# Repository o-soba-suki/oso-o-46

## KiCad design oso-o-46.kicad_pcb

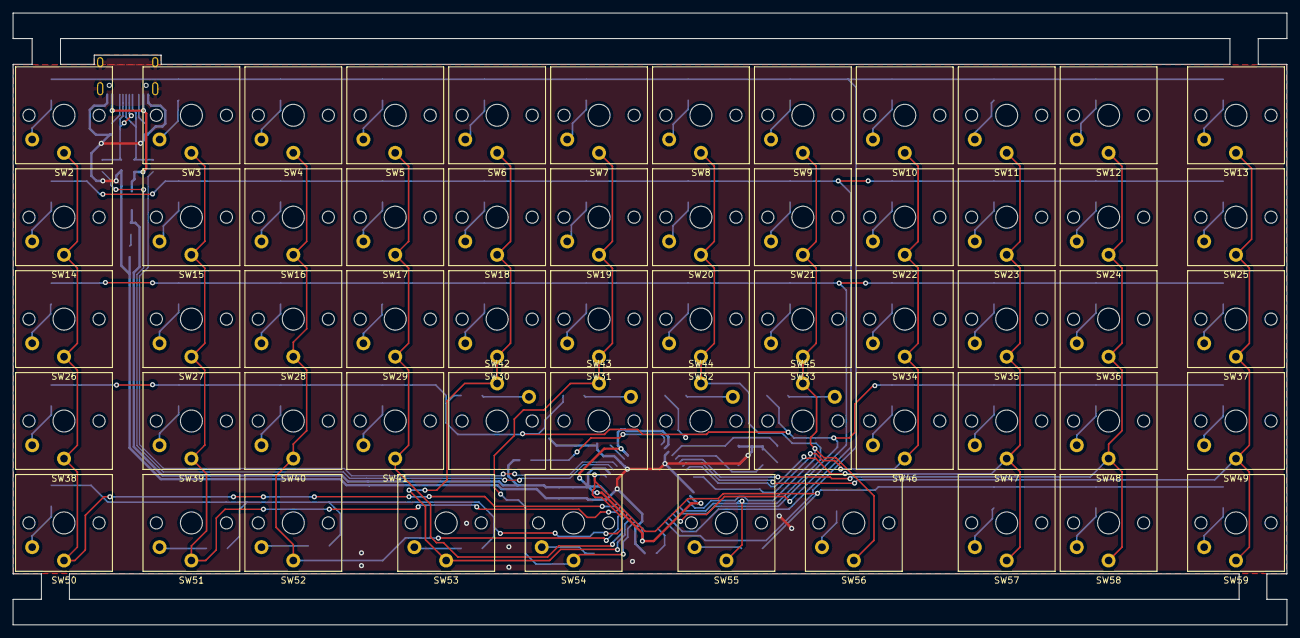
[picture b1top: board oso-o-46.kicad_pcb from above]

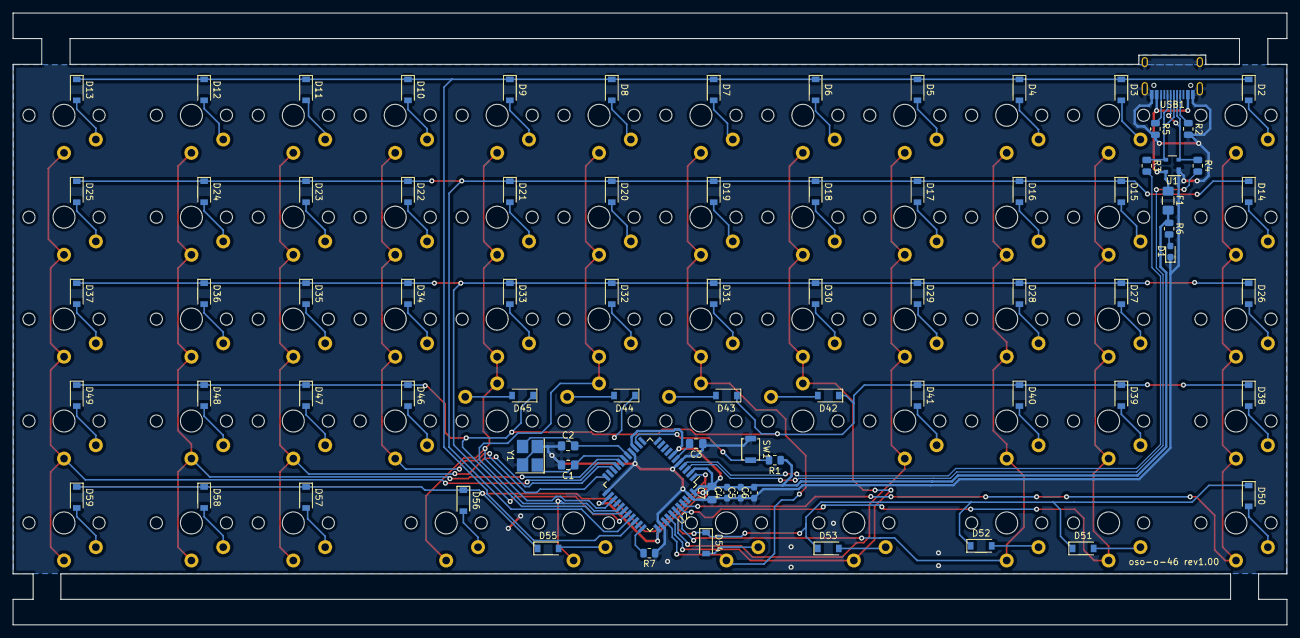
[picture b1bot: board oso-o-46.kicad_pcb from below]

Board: 2 copper layers, 200.0 x 96.0 mm, 137 parts (79 on the bottom side), 90 nets.

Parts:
C1, C2: 22u; C_0805_2012Metric_Pad1.18x1.45mm_HandSolder
C3: 1u; C_0805_2012Metric_Pad1.18x1.45mm_HandSolder
C4, C5, C6: 0.1u; C_0603_1608Metric_Pad1.08x0.95mm_HandSolder
C7: 10u; C_0805_2012Metric_Pad1.18x1.45mm_HandSolder
D1: LED; LED_0603_1608Metric_Pad1.05x0.95mm_HandSolder
D2, D3, D4, D5, D6, D7, D8, D9, D10, D11, D12, D13, D14, D15, D16, D17, D18, D19, D20, D21, D22, D23, D24, D25, D26, D27, D28, D29, D30, D31, D32, D33, D34, D35, D36, D37, D38, D39, D40, D41, D42, D43, D44, D45, D46, D47, D48, D49, D50, D51, D52, D53, D54, D55, D56, D57, D58, D59: D; D_SOD-123
F1: ASMD1206-150; Fuse_1206_3216Metric_Pad1.42x1.75mm_HandSolder
R1, R7: 10k; R_0805_2012Metric
R2, R5: 5.1k; R_0805_2012Metric
R3, R4: 22; R_0805_2012Metric
R6: 1k; R_0805_2012Metric
SW1: SW_Push; SW_SPST_B3U-1000P
SW2, SW3, SW4, SW5, SW6, SW7, SW8, SW9, SW10, SW11, SW12, SW13, SW14, SW15, SW16, SW17, SW18, SW19, SW20, SW21, SW22, SW23, SW24, SW25, SW26, SW27, SW28, SW29, SW30, SW31, SW32, SW33, SW34, SW35, SW36, SW37, SW38, SW39, SW40, SW41, SW42, SW43, SW44, SW45, SW46, SW47, SW48, SW49, SW50, SW51, SW52, SW53, SW54, SW55, SW56, SW57, SW58, SW59: SW_PUSH; SW_Kailh_Choc_V1
U1: PRTR5V0U2X; SOT-143
U2: ATmega32U4-A; TQFP-44_10x10mm_P0.8mm
USB1: HRO-TYPE-C-31-M-12; HRO-TYPE-C-31-M-12-Assembly
Y1: 16HMz; Crystal_SMD_3225-4Pin_3.2x2.5mm_HandSoldering

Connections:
+5V: C4.2, C5.2, C6.2, C7.2, F1.2, R1.1, R6.1, U2.2 (UVCC), U2.7 (VBUS), U2.14 (VCC), U2.24 (AVCC), U2.34 (VCC), U2.44 (AVCC)
COL01: SW2.1, SW14.1, SW26.1, SW38.1, SW50.1, U2.41 (PF0)
COL02: SW3.1, SW15.1, SW27.1, SW39.1, SW51.1, U2.40 (PF1)
COL03: SW4.1, SW16.1, SW28.1, SW40.1, SW52.1, U2.39 (PF4)
COL04: SW5.1, SW17.1, SW29.1, SW41.1, U2.38 (PF5)
COL05: SW6.1, SW18.1, SW30.1, SW42.1, SW53.1, U2.37 (PF6)
COL06: SW7.1, SW19.1, SW31.1, SW43.1, SW54.1, U2.36 (PF7)
COL07: SW8.1, SW20.1, SW32.1, SW44.1, SW55.1, U2.27 (PD7)
COL08: SW9.1, SW21.1, SW33.1, SW45.1, SW56.1, U2.25 (PD4)
COL09: SW10.1, SW22.1, SW34.1, SW46.1, U2.22 (PD5)
COL10: SW11.1, SW23.1, SW35.1, SW47.1, SW57.1, U2.20 (PD2)
COL11: SW12.1, SW24.1, SW36.1, SW48.1, SW58.1, U2.18 (PD0)
COL12: SW13.1, SW25.1, SW37.1, SW49.1, SW59.1, U2.19 (PD1)
D+: R3.2, U2.4 (D+)
D-: R4.2, U2.3 (D-)
GND: C1.2, C2.1, C3.1, C4.1, C5.1, C6.1, C7.1, D1.1 (K), R2.2, R5.2, R7.1, SW1.1, U1.1 (GND), U2.5 (UGND), U2.15 (GND), U2.23 (GND), U2.35 (GND), U2.43 (GND), USB1.1 (GND), USB1.12 (GND), USB1.13 (SHIELD), Y1.2, Y1.4
unnamed: C1.1, U2.17 (XTAL1), Y1.1
unnamed: C2.2, U2.16 (XTAL2), Y1.3
unnamed: C3.2, U2.6 (UCAP)
unnamed: D1.2 (A), R6.2
unnamed: D2.2 (A), SW2.2
unnamed: D3.2 (A), SW3.2
unnamed: D4.2 (A), SW4.2
unnamed: D5.2 (A), SW5.2
unnamed: D6.2 (A), SW6.2
unnamed: D7.2 (A), SW7.2
unnamed: D8.2 (A), SW8.2
unnamed: D9.2 (A), SW9.2
unnamed: D10.2 (A), SW10.2
unnamed: D11.2 (A), SW11.2
unnamed: D12.2 (A), SW12.2
unnamed: D13.2 (A), SW13.2
unnamed: D14.2 (A), SW14.2
unnamed: D15.2 (A), SW15.2
unnamed: D16.2 (A), SW16.2
unnamed: D17.2 (A), SW17.2
unnamed: D18.2 (A), SW18.2
unnamed: D19.2 (A), SW19.2
unnamed: D20.2 (A), SW20.2
unnamed: D21.2 (A), SW21.2
unnamed: D22.2 (A), SW22.2
unnamed: D23.2 (A), SW23.2
unnamed: D24.2 (A), SW24.2
unnamed: D25.2 (A), SW25.2
unnamed: D26.2 (A), SW26.2
unnamed: D27.2 (A), SW27.2
unnamed: D28.2 (A), SW28.2
unnamed: D29.2 (A), SW29.2
unnamed: D30.2 (A), SW30.2
unnamed: D31.2 (A), SW31.2
unnamed: D32.2 (A), SW32.2
unnamed: D33.2 (A), SW33.2
unnamed: D34.2 (A), SW34.2
unnamed: D35.2 (A), SW35.2
unnamed: D36.2 (A), SW36.2
unnamed: D37.2 (A), SW37.2
unnamed: D38.2 (A), SW38.2
unnamed: D39.2 (A), SW39.2
unnamed: D40.2 (A), SW40.2
unnamed: D41.2 (A), SW41.2
unnamed: D42.2 (A), SW42.2
unnamed: D43.2 (A), SW43.2
unnamed: D44.2 (A), SW44.2
unnamed: D45.2 (A), SW45.2
unnamed: D46.2 (A), SW46.2
unnamed: D47.2 (A), SW47.2
unnamed: D48.2 (A), SW48.2
unnamed: D49.2 (A), SW49.2
unnamed: D50.2 (A), SW50.2
unnamed: D51.2 (A), SW51.2
unnamed: D52.2 (A), SW52.2
unnamed: D53.2 (A), SW53.2
unnamed: D54.2 (A), SW54.2
unnamed: D55.2 (A), SW55.2
unnamed: D56.2 (A), SW56.2
unnamed: D57.2 (A), SW57.2
unnamed: D58.2 (A), SW58.2
unnamed: D59.2 (A), SW59.2
unnamed: R2.1, USB1.4 (CC1)
unnamed: R3.1, U1.3 (IO2), USB1.6 (DP1), USB1.8 (DP2)
unnamed: R4.1, U1.2 (IO1), USB1.5 (DN2), USB1.7 (DN1)
unnamed: R5.1, USB1.10 (CC2)
unnamed: R7.2, U2.33 (~HWB/PE2)
RESET: R1.2, SW1.2, U2.13 (~RESET)
ROW01: D2.1 (K), D3.1 (K), D4.1 (K), D5.1 (K), D6.1 (K), D7.1 (K), D8.1 (K), D9.1 (K), D10.1 (K), D11.1 (K), D12.1 (K), D13.1 (K), U2.31 (PC6)
ROW02: D14.1 (K), D15.1 (K), D16.1 (K), D17.1 (K), D18.1 (K), D19.1 (K), D20.1 (K), D21.1 (K), D22.1 (K), D23.1 (K), D24.1 (K), D25.1 (K), U2.30 (PB6)
ROW03: D26.1 (K), D27.1 (K), D28.1 (K), D29.1 (K), D30.1 (K), D31.1 (K), D32.1 (K), D33.1 (K), D34.1 (K), D35.1 (K), D36.1 (K), D37.1 (K), U2.29 (PB5)
ROW04: D38.1 (K), D39.1 (K), D40.1 (K), D41.1 (K), D42.1 (K), D43.1 (K), D44.1 (K), D45.1 (K), D46.1 (K), D47.1 (K), D48.1 (K), D49.1 (K), U2.28 (PB4)
ROW05: D50.1 (K), D51.1 (K), D52.1 (K), D53.1 (K), D54.1 (K), D55.1 (K), D56.1 (K), D57.1 (K), D58.1 (K), D59.1 (K), U2.1 (PE6)
VCC: F1.1, U1.4 (VCC), USB1.2 (VBUS), USB1.11 (VBUS)

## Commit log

2022-10-17 Capacitor capacitance was incorrect.
